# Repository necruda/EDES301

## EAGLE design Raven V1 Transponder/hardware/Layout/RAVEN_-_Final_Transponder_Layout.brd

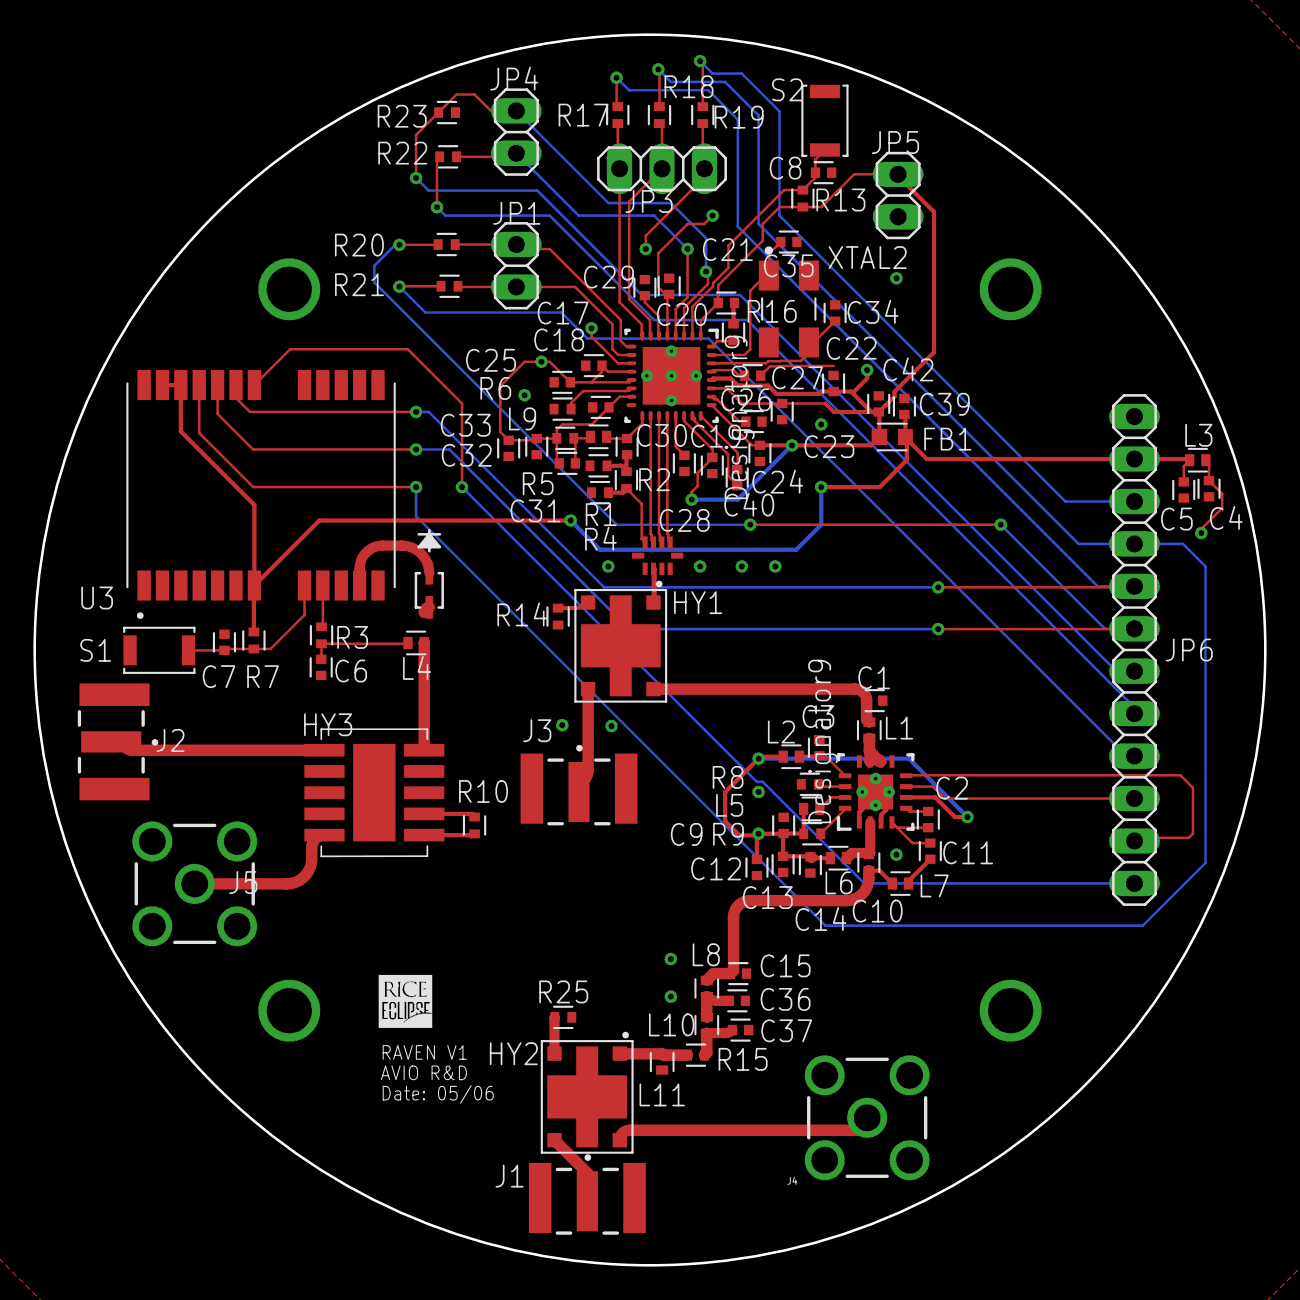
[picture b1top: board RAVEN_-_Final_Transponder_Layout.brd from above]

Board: 4 copper layers, 73.7 x 73.7 mm, 98 parts (0 on the bottom side), 62 nets.

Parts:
C1: 0.8pF; CAPC1005X60
C2: 12pF; CAPC1005X60
C3, C11, C30, C34, C35: 15pF; CAPC1005X60
C4: 10µF; CAPC1005X60
C5: 220pF; CAPC1005X60
C6, C7, C8: 100nF; CAPC1005X60
C9: 27pF; CAPC1005X60
C10, C14: 47pF; CAPC1005X60
C12: 1µF; CAPC1005X60
C13: 1nF; CAPC1005X60
C15: 3.3pF; CAPC1005X60
C17, C18, C19, C20, C21, C22, C23, C24, C25, C26, C27: 47nF; CAPC1005X60
C28, C32: 10nF; CAPC1005X60
C29: 220nF; CAPC1005X60
C31: 33pF; CAPC1005X60
C33: 100pF; CAPC1005X60
C36: 7.5pF; CAPC1005X60
C37: DNP; CAPC1005X60
C39: 100µF; CAPC1005X60
C40: 1.8nF; CAPC1005X60
C42: 2.2µF; CAPC1005X60
CR1: PESD5V0S1BASOD323_NEX; SOD323_NEX
FB1: FBCHIP-0603(1608-METRIC); BEADC1608X95N
H1, H2, H3, H4: MountingHole; MOUNTINGHOLE_MOUNTINGHOLE_2.7MM_M2.5
HY1, HY2: XC0900P-10S; COUPLER_XC0900P-10S
HY3: BDCA-10-25+; BDCA1025
J1, J2, J3: SMA-J-P-H-ST-EM1; SAMTEC_SMA-J-P-H-ST-EM1
J4, J5: SMA-J-P-X-RA-TH1; SAMTEC_SMA-J-P-X-RA-TH1
JP1, JP4, JP5: PINHD-1X2; 1X02
JP3: PINHD-1X3; 1X03
JP6: PINHD-1X12; 1X12
L1, L3: 10nH; INDC1006X60N
L2: 1.5nH; INDC1006X60N
L4: 27 nH; INDC1006X60N
L5: 15nH; INDC1006X60N
L6: 22nH; INDC1006X60N
L7: 7.5nH; INDC1006X60N
L8: 2.9nH; INDC1006X60N
L9: 8.2nH; INDC1006X60N
L10: 9.1nH; INDC1006X60N
L11: 12nH; INDC1006X60N
R1, R4: 82Ω; RESC1005X40
R2: 91Ω; RESC1005X40
R3, R5: 10Ω; RESC1005X40
R6: 56k; RESC1005X40
R7, R13: 10k; RESC1005X40
R8: 3.3k; RESC1005X40
R9: 47; RESC1005X40
R10, R14, R25: 50Ω; RESC1005X40
R15, R16: 0Ω; RESC1005X40
R17, R18, R19, R20, R21, R22, R23: 0; RESC1005X40
S1, S2: B3U-X000B3U-1000P(M)1000P(M); B3U-1000P(M)
U1: LFD21868MMF1D386LFD21868MMF1D386_MUR; LFD21868MMF1D386_MUR
U2: CC1200RHBRRHB0032E; RHB0032E
U3: NEO-M9N-00B; XCVR_NEO-M9N-00B
U5: CC1190RGVRRGV0016A; RGV0016A
XTAL2: 32 MHz Crystal Oscillator; OSCSC500X320X110-4N

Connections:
3.3V: C5.2, C39.2, FB1.1, JP6.2, L3.2, R7.2, U3.7, U3.22, U3.23
ANT_IN: HY3.1, HY3.6, J5.1, L4.2
CLK: JP3.1, JP6.5, R17.1, R17.2, U2.8, U3.19
CS_GPS: JP6.12, U3.18
CS_RFIC: JP3.3, JP6.3, R19.1, R19.2, U2.11
GND: C1.1, C3.1, C4.1, C5.1, C6.2, C7.1, C8.2, C9.1, C12.1, C13.1, C14.1, C15.1, C17.2, C18.2, C19.2, C20.2, C21.2, C22.2, C23.2, C24.2, C25.2, C26.2, C27.2, C28.2, C29.2, C32.1, C33.1, C34.2, C35.1, C36.1, C37.1, C39.1, C42.1, HY1.5, HY2.5, HY3.2, HY3.3, HY3.4, HY3.7, HY3.8, HY3.9, HY3.11, J1.2_1, J1.2_2, J1.3_1, J1.3_2, J2.2_1, J2.2_2, J2.3_1, J2.3_2, J3.2_1, J3.2_2, J3.3_1, J3.3_2, J4.2, J4.3, J4.4, J4.5, J5.2, J5.3, J5.4, J5.5, JP6.1, L11.1, R1.1, R4.1, R6.2, R8.1, R10.1, R14.1, R16.2, R25.1, S1.2, S2.1, U1.1, U1.4, U1.5, U1.10, U2.33, U3.2, U3.10, U3.12, U3.13, U3.24, U5.1, U5.3, U5.9, U5.12, U5.17, XTAL2.2, XTAL2.4
LNA_EN_LP: JP6.10, U5.7
LNA_N: U1.6, U2.20
LNA_P: U1.7, U2.19
MISO: JP6.6, R20.2, U3.20
MISO_2: JP1.1, R20.1, U2.9
MOSI: JP3.2, JP6.4, R18.1, R18.2, U2.7, U3.21
unnamed: HY1.1, U1.2
unnamed: C1.2, HY1.2, L1.2
unnamed: R8.2, U5.14
unnamed: L5.1, U5.15
unnamed: C2.2, C11.1, U5.4
unnamed: C2.1, U5.5
unnamed: C3.2, L2.1, U5.13
unnamed: CR1.1, U3.11
unnamed: R9.1, U5.16
unnamed: C7.2, R7.1, S1.1, U3.8
unnamed: C10.2, L6.1, U5.2
unnamed: C11.2, L7.1
unnamed: C6.1, L4.1, R3.2
unnamed: HY1.4, R14.2
unnamed: HY1.3, J3.1
unnamed: HY3.10, J2.1
unnamed: HY3.5, R10.2
unnamed: C26.1, U2.26
unnamed: C28.1, U2.21
unnamed: C29.1, U2.6
unnamed: R16.1, U2.32
unnamed: C27.1, U2.29
unnamed: C30.2, L9.2, U2.17
unnamed: C31.2, L9.1, R5.2
unnamed: C30.1, R1.2, R2.2
unnamed: C36.2, L8.1, L10.2
unnamed: C34.1, U2.30, XTAL2.3
unnamed: C35.2, U2.31, XTAL2.1
unnamed: R6.1, U2.14
unnamed: C40.1, U2.23
unnamed: C40.2, U2.24
unnamed: C37.2, L10.1, R15.1
unnamed: HY2.2, J4.1
unnamed: HY2.3, J1.1
unnamed: HY2.4, R25.2
unnamed: HY2.1, L11.2, R15.2
unnamed: C10.1, C15.2, L7.2, L8.2
PA_EN_LP: JP6.11, U5.8
PA_IN: L1.1, U5.10, U5.11
RF_GPIO0: JP6.9, R21.2
RF_GPIO2: JP6.8, R22.2
RF_GPIO2_IN: JP4.1, R22.1, U2.4
RF_GPIO3: JP4.2, JP6.7, R23.1, U2.3
RF_GPIO_IN_0: JP1.2, R21.1, U2.10
RF_RESET_N: C8.1, R13.2, S2.2, U2.2
TRX: U1.8, U2.18
TXPA: R2.1, R4.2, U1.9
VCC_RF: R3.1, U3.9
VDD_CC1190: C4.2, C9.2, C12.2, C13.2, C14.2, L2.2, L3.1, L5.2, L6.2, R9.2, U5.6
VDD_CC1200: C17.1, C18.1, C19.1, C20.1, C21.1, C22.1, C23.1, C24.1, C25.1, C31.1, C32.2, C33.2, C42.2, FB1.2, JP5.1, R5.1, R13.1, U2.1, U2.5, U2.12, U2.13, U2.15, U2.22, U2.25, U2.27, U2.28

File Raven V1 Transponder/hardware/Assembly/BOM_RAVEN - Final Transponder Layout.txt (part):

Partlist exported from Fusion Hub: Avio Comms   Project: Default Project  Board: RAVEN - Final Transponder Layout at 5/7/26 2:47 AM

Qty Value                                Device                                           Package                              Parts                                                 Description                                                                                   CATEGORY     COPYRIGHT                                                CURRENT_RATING DATASHEET                                                   DC_RESISTANCE DESCRIPTION                                                           FOOTPRINT                            FREQUENCY                                    FREQUENCY_STABILITY HEIGHT IMPEDANCE LOAD_CAPACITANCE MANUFACTURER                  MANUFACTURER_NAME MANUFACTURER_PART_NUMBER MATERIAL_CORE MAXIMUM_PACKAGE_HEIGHT MOUSER_PART_NUMBER MOUSER_PRICE-STOCK MPN                  OPERATING_TEMP  OPERATING_TEMPERATURE                                                                                PACKAGE_SIZE  PACKAGE_TYPE  PARTREV PART_STATUS PITCH           REFDES ROHS      ROHS_COMPLIANT SERIES STANDARD                     SUB-CATEGORY SUBCATEGORY        TEMPERATURE_COEFFICIENT THERMALLOSS TOLERANCE TYPE       VOLTAGE_RATING
7   0                                    R_CHIP-0402(1005-METRIC)                         RESC1005X40                          R17, R18, R19, R20, R21, R22, R23                     Resistor Fixed - Generic                                                                      Resistors                                                                                                                                                      Chip Resistor 1.05 X 0.54 X 0.40 mm body 0402(1005-METRIC) Package                                                                                                                                                                                                                                                                                                                                                                                                                                          0402          Surface Mount                                                                                                                                                                                                                
1   0.8pF                                C_CHIP-0402(1005-METRIC)                         CAPC1005X60                          C1                                                    Capacitor - Generic                                                                           Capacitor                                                                                                                                                                                                                                                                                                                                                                                                                                                                                                                                                                                                                                                                  0402          Surface Mount                                                                                                                      Ceramic Capacitors                                               MLCC                     
2   0Ω                                   R_CHIP-0402(1005-METRIC)                         RESC1005X40                          R15, R16                                              Resistor Fixed - Generic                                                                      Resistors                                                                                                                                                      Chip Resistor 1.05 X 0.54 X 0.40 mm body 0402(1005-METRIC) Package                                                                                                                                                                                                                                                                                                                                                                                                                                          0402          Surface Mount                                                                                                                                                                                                                
1   1.5nH                                L_CHIP-0402(1006-METRIC)                         INDC1006X60N                         L2                                                    Inductor Fixed - Generic                                                                      Inductors                                                                                                                                                      Chip 1.00 X 0.60 X 0.60 mm body 0402(1006-METRIC)                                                                                                                                                                                                                                                                                                                                                                                                                                                           0402          Surface Mount                                                                                                                                                                                                                
1   1.8nF                                C_CHIP-0402(1005-METRIC)                         CAPC1005X60                          C40                                                   Capacitor - Generic                                                                           Capacitor                                                                                                                                                                                                                                                                                                                                                                                                                                                                                                                                                                                                                                                                                                                                                                                                                                                                                                             
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
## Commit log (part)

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2026-02-23 New Folder
2026-02-23 Add project_01 folder with README and proposal PPT
2026-02-24 Add docs folder and project proposal
2026-03-04 Added USR3 LED blink program at 5 Hz
2026-03-04 Added Button directory and program
2026-03-04 Added simple calc, people counter files, ht166k33
2026-04-26 Delete project_01 directory
    I'm just in the process of replacing the files with the final files
2026-04-26 Add files via upload
    This is the project_01 folder replaced with all the files I used for my project, the main software (components folder), samples, projects (load projects folder), and tests (folder of scripts used to 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
2026-04-26 Update README.md
    Updating operating software instructions, just missing the building the software instructions, that will be brutal
2026-04-26 Update README.md
    Inserted instructions for threaded input
2026-04-26 Update README.md
    Have made descriptions for all the hardware based code except the screen, so I'm missing the screen, the audio, and the actual OS that connects everything
2026-04-26 Delete FINAL MiniDrum/components/hardware_diagnostic.py
    I'm moving this file to tests folder because I think it fits more in that category of code
2026-04-26 Add files via upload
    Completing the moving of hardware_diagnostic.py to the tests folder
2026-04-27 Update README.md
    Finished the whole README.md document, it now has complete and detailed instructions on how to make the whole software.
2026-04-27 Update README.md
    Added to audio manager and project manager for clarifications on their respective folders
2026-04-27 Update README.md
    making it pretty
2026-04-27 Update README.md
    updated name
2026-04-27 Update README.md
    updated thread manager
2026-05-06 renaming, and making read.me file for project 2
2026-05-07 Added pptx presentation with all the block diagrams
2026-05-07 Delete project_01/docs/Alejandro_Andrade_EDES301_project_01_proposal (1).pptx
    deleting incomplete presentation
2026-05-07 updating readme
2026-05-07 readme correction
2026-05-07 title update for readme
2026-05-07 Delete python/blink_led/blink_USR3.py
    deleting the file
2026-05-07 added name to simple calc
2026-05-07 finishing project_02

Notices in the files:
parts and their libraries:
COPYRIGHT: Copyright (C) 2025 Ultra Librarian. All rights reserved.
COPYRIGHT: Copyright (C) 2026 Ultra Librarian. All rights reserved.
